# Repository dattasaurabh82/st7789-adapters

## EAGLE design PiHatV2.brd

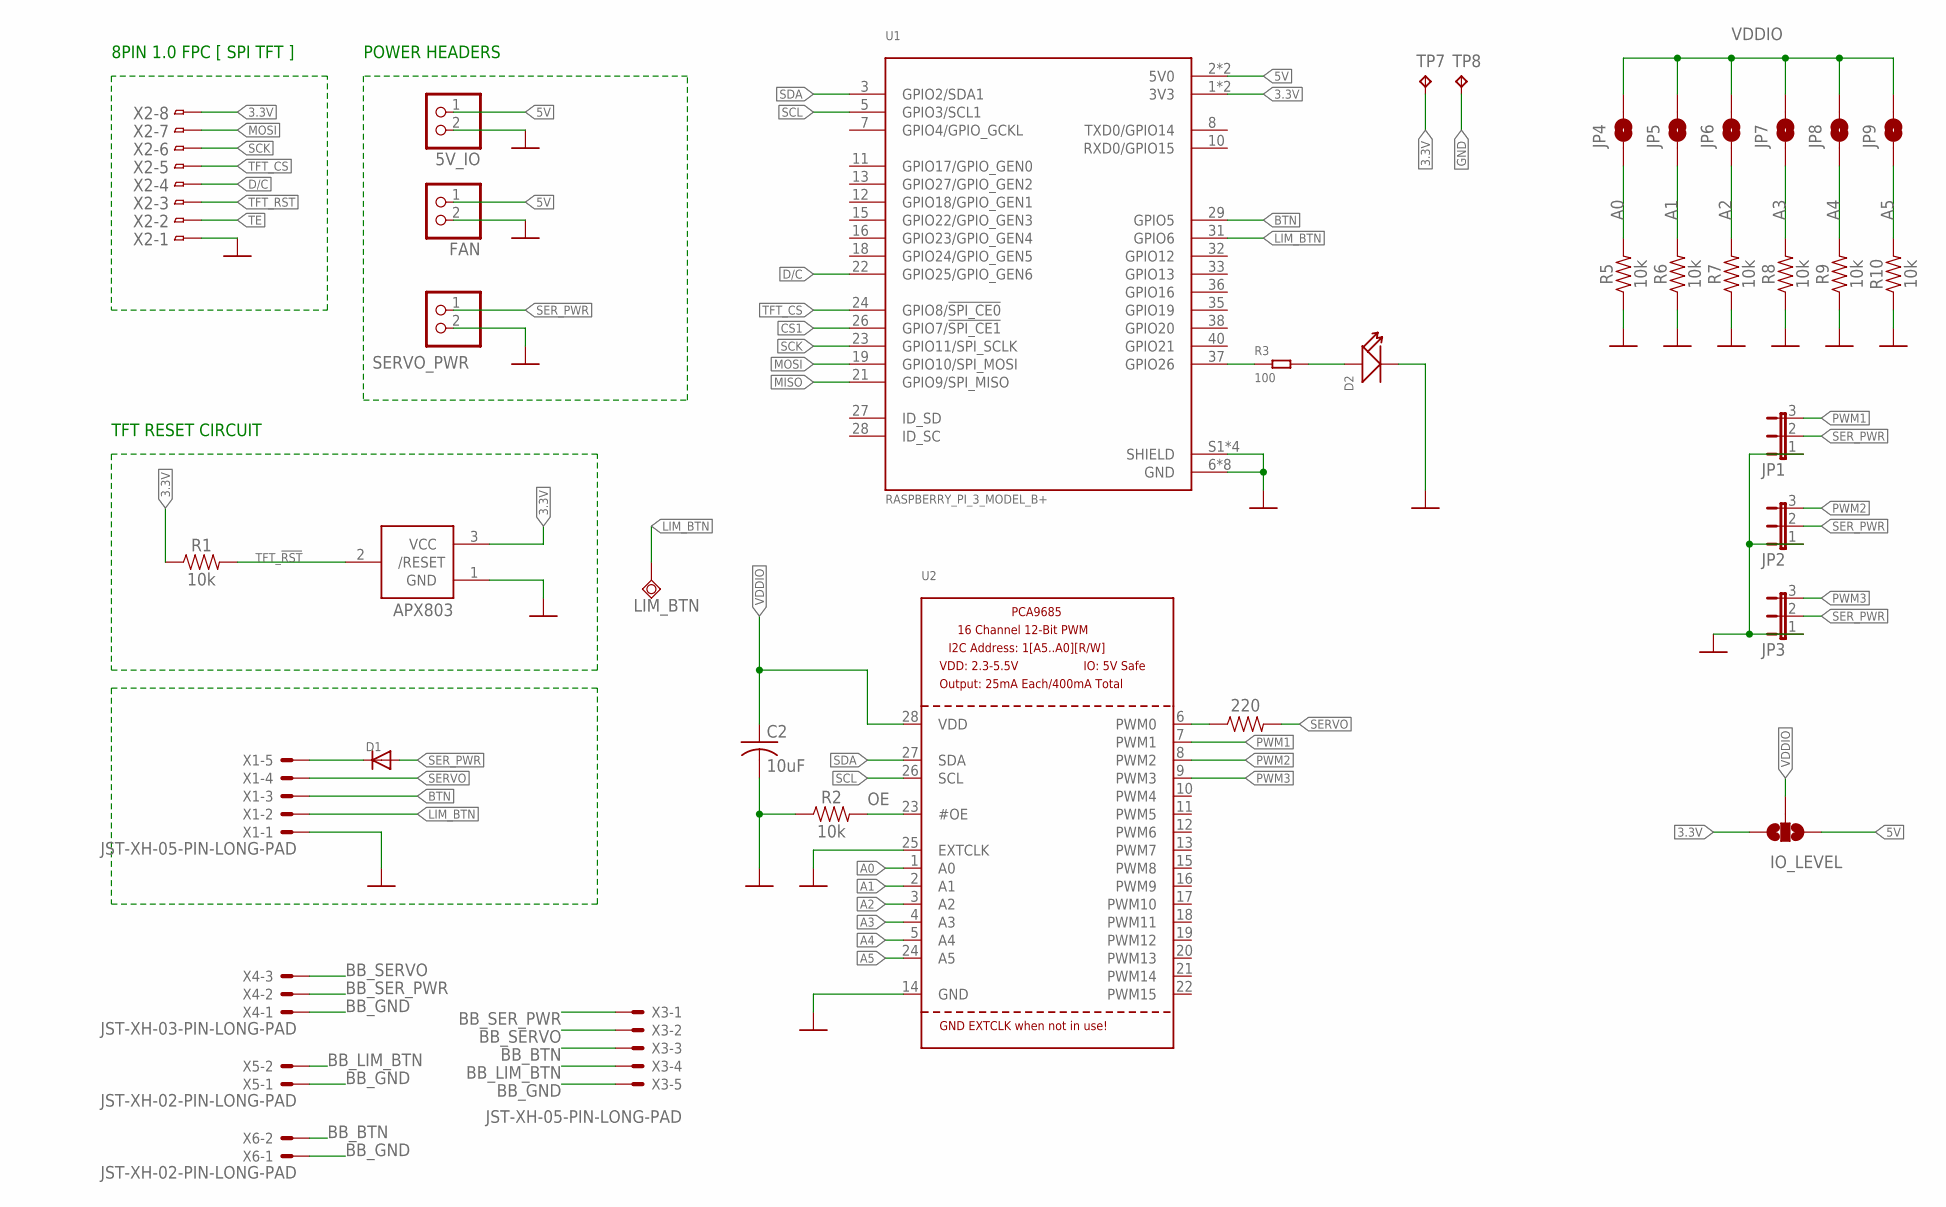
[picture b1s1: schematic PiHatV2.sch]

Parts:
5V_IO: ONBOARDCONTROLINTERFACE_LED-BADGE_SCHEMATIC_ADAFR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; ONBOARDCONTROLINTERFACE_LED-BADGE_SCHEMATIC_ADAFRUIT_JST-PH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
APX803: ADAFRUIT_AXP083-SAG; ADAFRUIT_SOT23
C2: 10uF; C0805K
D1: DIODESMA; SMADIODE
D2: BLUE-0603; LED-0603
FAN: ONBOARDCONTROLINTERFACE_LED-BADGE_SCHEMATIC_ADAFR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; ONBOARDCONTROLINTERFACE_LED-BADGE_SCHEMATIC_ADAFRUIT_JST-PH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
IO_LEVEL: JUMPER-SMT_3_NO_NO-SILK; SMT-JUMPER_3_NO_NO-SILK
JP1, JP2, JP3: LED-BADGE_SCHEMATIC_JUMPER_JP2E; LED-BADGE_SCHEMATIC_JUMPER_JP2
JP4, JP5, JP6, JP7, JP8, JP9: JUMPER-SMT_2_NO_NO-SILK; SMT-JUMPER_2_NO_NO-SILK
LIM_BTN: TESTPAD_TPSQB1,27; TESTPAD_B1,27
R1, R2, R5, R6, R7, R8, R9, R10: 10k; ARDUINO_3V_TTL_INTERFACE_2_PI_SPARKFUN-RESISTORS_0603:1
R3: 100; R0805
R4: 220; ARDUINO_3V_TTL_INTERFACE_2_PI_SPARKFUN-RESISTORS_0603:1
SERVO_PWR: ONBOARDCONTROLINTERFACE_LED-BADGE_SCHEMATIC_ADAFR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; ONBOARDCONTROLINTERFACE_LED-BADGE_SCHEMATIC_ADAFRUIT_JST-PH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
TP7, TP8: TPB2,54; B2,54
U1: RASPBERRY_PI_3_MODEL_B+; MODULE_RASPBERRY_PI_3_MODEL_B+
U2: PCA9685; TSSOP28
X1, X3: JST-XH-05-PIN-LONG-PAD; JST-XH-05-PACKAGE-LONG-PAD
X2: SCREENBREAKOUT_SCREENBREAKOUT_LEDMATRIXFPCCONNECT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; SCREENBREAKOUT_SCREENBREAKOUT_LEDMATRIXFPCCONNECTOR_CON-HIR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
X4: JST-XH-03-PIN-LONG-PAD; JST-XH-03-PACKAGE-LONG-PAD
X5, X6: JST-XH-02-PIN-LONG-PAD; JST-XH-02-PACKAGE-LONG-PAD

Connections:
3.3V: APX803.3 (VCC), IO_LEVEL.3, R1.1, TP7.TP, U1.1 (3V3), U1.17 (3V3), X2.8
5V: 5V_IO.1 (2), FAN.1 (2), IO_LEVEL.1, U1.2 (5V0), U1.4 (5V0)
A0: JP4.1, R5.2, U2.1 (A0)
A1: JP5.1, R6.2, U2.2 (A1)
A2: JP6.1, R7.2, U2.3 (A2)
A3: JP7.1, R8.2, U2.4 (A3)
A4: JP8.1, R9.2, U2.5 (A4)
A5: JP9.1, R10.2, U2.24 (A5)
BB_BTN: X3.3, X6.2
BB_GND: X3.5, X4.1, X5.1, X6.1
BB_LIM_BTN: X3.4, X5.2
BB_SERVO: X3.2, X4.3
BB_SER_PWR: X3.1, X4.2
BTN: U1.29 (GPIO5), X1.3
CS1: U1.26 (GPIO7/!SPI_CE1!)
D/C: U1.22 (GPIO25/GPIO_GEN6), X2.4
GND: 5V_IO.2 (1), APX803.1 (GND), C2.2, D2.-, FAN.2 (1), JP1.1, JP2.1, JP3.1, R2.1, R5.1, R6.1, R7.1, R8.1, R9.1, R10.1, SERVO_PWR.2 (1), TP8.TP, U1.6 (GND), U1.9 (GND), U1.14 (GND), U1.20 (GND), U1.25 (GND), U1.30 (GND), U1.34 (GND), U1.39 (GND), U1.S1 (SHIELD), U1.S2 (SHIELD), U1.S3 (SHIELD), U1.S4 (SHIELD), U2.14 (GND), U2.25 (EXTCLK), X1.1, X2.1
LIM_BTN: LIM_BTN.TP, U1.31 (GPIO6), X1.2
MISO: U1.21 (GPIO9/SPI_MISO)
MOSI: U1.19 (GPIO10/SPI_MOSI), X2.7
unnamed: R4.1, U2.6 (PWM0)
unnamed: D1.C, X1.5
unnamed: R3.1, U1.37 (GPIO26)
unnamed: D2.+, R3.2
OE: R2.2, U2.23 (#OE)
PWM1: JP1.3, U2.7 (PWM1)
PWM2: JP2.3, U2.8 (PWM2)
PWM3: JP3.3, U2.9 (PWM3)
SCK: U1.23 (GPIO11/SPI_SCLK), X2.6
SCL: U1.5 (GPIO3/SCL1), U2.26 (SCL)
SDA: U1.3 (GPIO2/SDA1), U2.27 (SDA)
SERVO: R4.2, X1.4
SER_PWR: D1.A, JP1.2, JP2.2, JP3.2, SERVO_PWR.1 (2)
TE: X2.2
TFT_!RST: APX803.2 (/RESET), R1.2, X2.3
TFT_CS: U1.24 (GPIO8/!SPI_CE0!), X2.5
VDDIO: C2.1, IO_LEVEL.2, JP4.2, JP5.2, JP6.2, JP7.2, JP8.2, JP9.2, U2.28 (VDD)

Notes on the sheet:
TFT RESET CIRCUIT
8PIN 1.0 FPC [ SPI TFT ]
POWER HEADERS

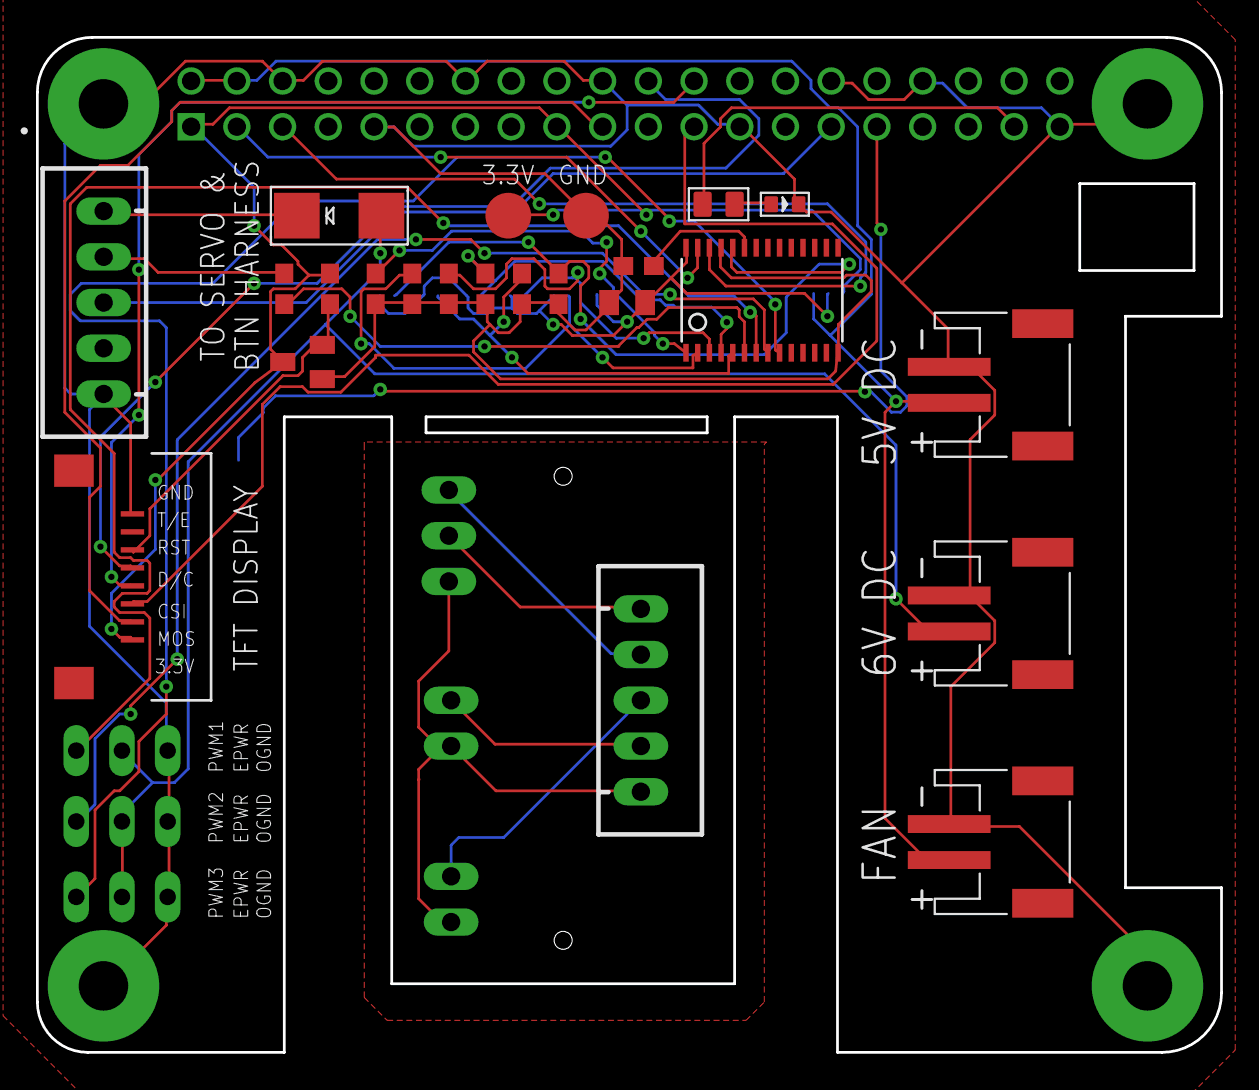
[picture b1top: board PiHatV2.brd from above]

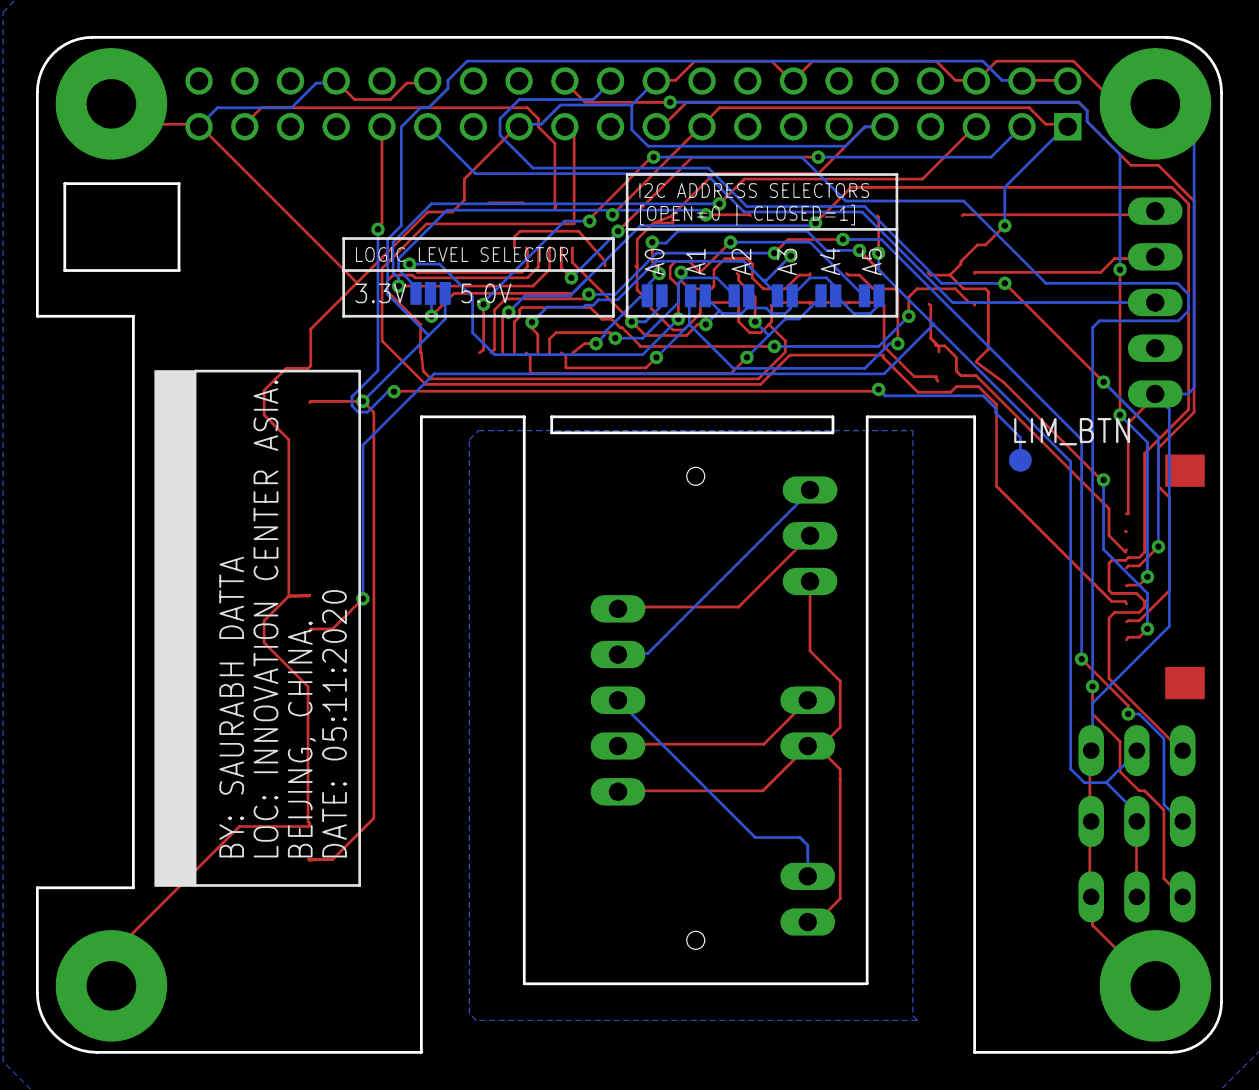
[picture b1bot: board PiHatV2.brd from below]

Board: 2 copper layers, 65.8 x 56.4 mm, 38 parts (8 on the bottom side), 34 nets.

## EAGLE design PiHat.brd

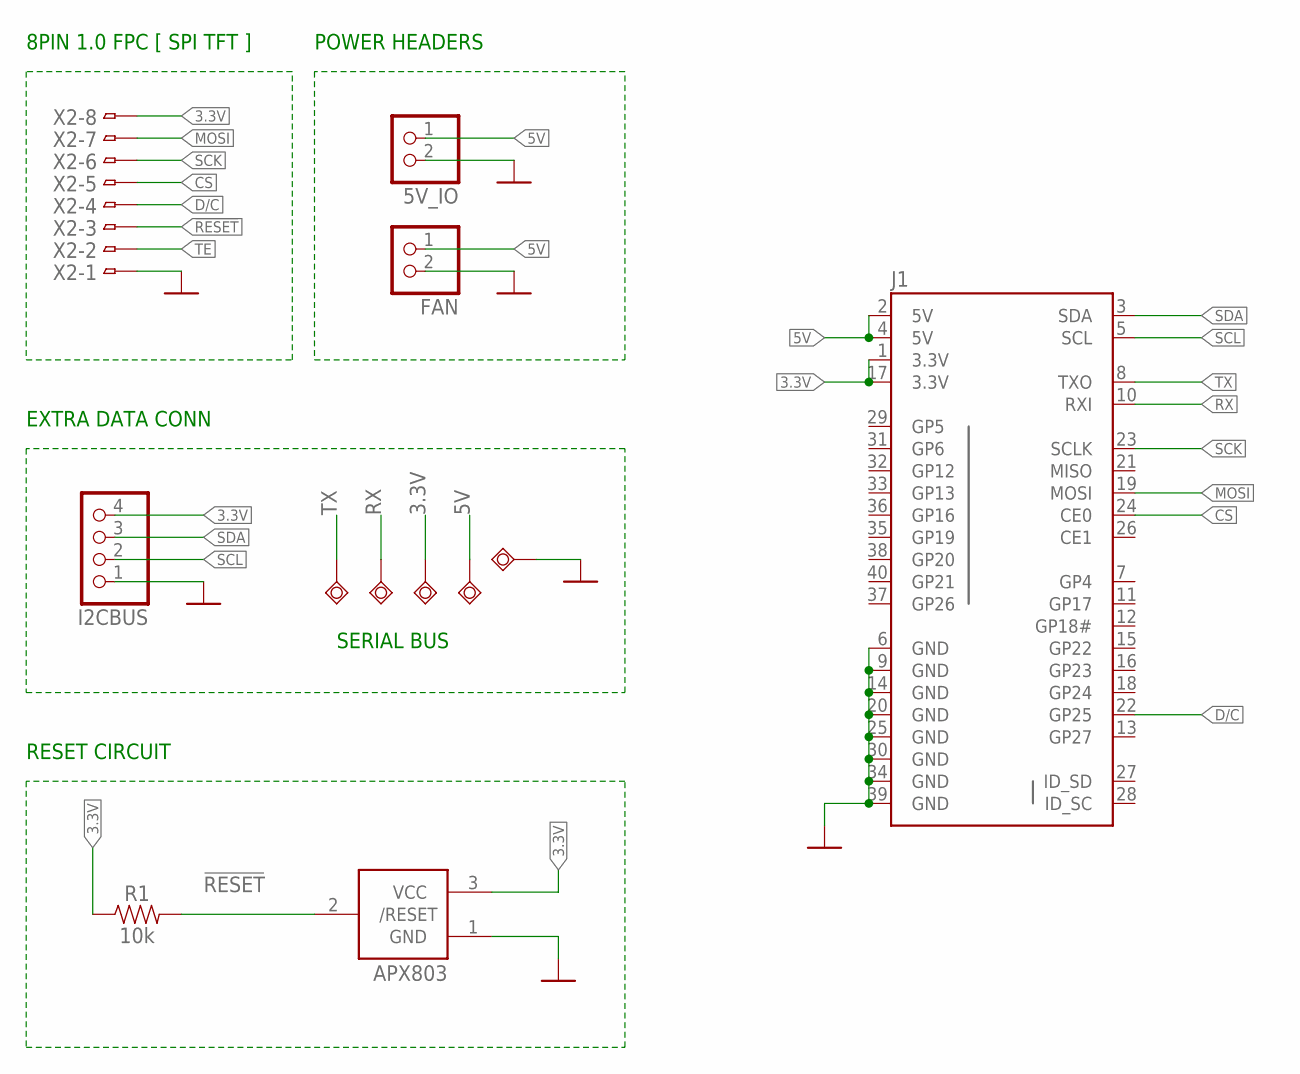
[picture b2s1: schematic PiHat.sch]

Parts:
5V_IO: ONBOARDCONTROLINTERFACE_LED-BADGE_SCHEMATIC_ADAFR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; ONBOARDCONTROLINTERFACE_LED-BADGE_SCHEMATIC_ADAFRUIT_JST-PH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
APX803: ADAFRUIT_AXP083-SAG; ADAFRUIT_SOT23
FAN: ONBOARDCONTROLINTERFACE_LED-BADGE_SCHEMATIC_ADAFR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; ONBOARDCONTROLINTERFACE_LED-BADGE_SCHEMATIC_ADAFRUIT_JST-PH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
I2CBUS: MICROBUILDER_JST_4PIN; MICROBUILDER_JSTPH4
J1: DESTINYSENSORFINAL_SPARKFUN-CONNECTORS_RASPBERRYP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; DESTINYSENSORFINAL_SPARKFUN-CONNECTORS_2X20
R1: 10k; ARDUINO_3V_TTL_INTERFACE_2_PI_SPARKFUN-RESISTORS_0603:1
TP1, TP2, TP3, TP4, TP5: DESTINYSENSORFINAL_ARDUINO_3V_TTL_INTERFACE_2_PI_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; DESTINYSENSORFINAL_ARDUINO_3V_TTL_INTERFACE_2_PI_TESTPAD_TP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
X2: SCREENBREAKOUT_SCREENBREAKOUT_LEDMATRIXFPCCONNECT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; SCREENBREAKOUT_SCREENBREAKOUT_LEDMATRIXFPCCONNECTOR_CON-HIR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

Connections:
3.3V: APX803.3 (VCC), I2CBUS.4, J1.1 (3.3V), J1.17 (3.3V), R1.1, TP3.TP, X2.8
5V: 5V_IO.1 (2), FAN.1 (2), J1.2 (5V), J1.4 (5V), TP4.TP
!RESET: APX803.2 (/RESET), R1.2, X2.3
CS: J1.24 (CE0), X2.5
D/C: J1.22 (GP25), X2.4
GND: 5V_IO.2 (1), APX803.1 (GND), FAN.2 (1), I2CBUS.1, J1.6 (GND), J1.9 (GND), J1.14 (GND), J1.20 (GND), J1.25 (GND), J1.30 (GND), J1.34 (GND), J1.39 (GND), TP5.TP, X2.1
MOSI: J1.19 (MOSI), X2.7
RX: J1.10 (RXI), TP2.TP
SCK: J1.23 (SCLK), X2.6
SCL: I2CBUS.2, J1.5 (SCL)
SDA: I2CBUS.3, J1.3 (SDA)
TE: X2.2
TX: J1.8 (TXO), TP1.TP

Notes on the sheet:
SERIAL BUS
RESET CIRCUIT
8PIN 1.0 FPC [ SPI TFT ]
POWER HEADERS
EXTRA DATA CONN

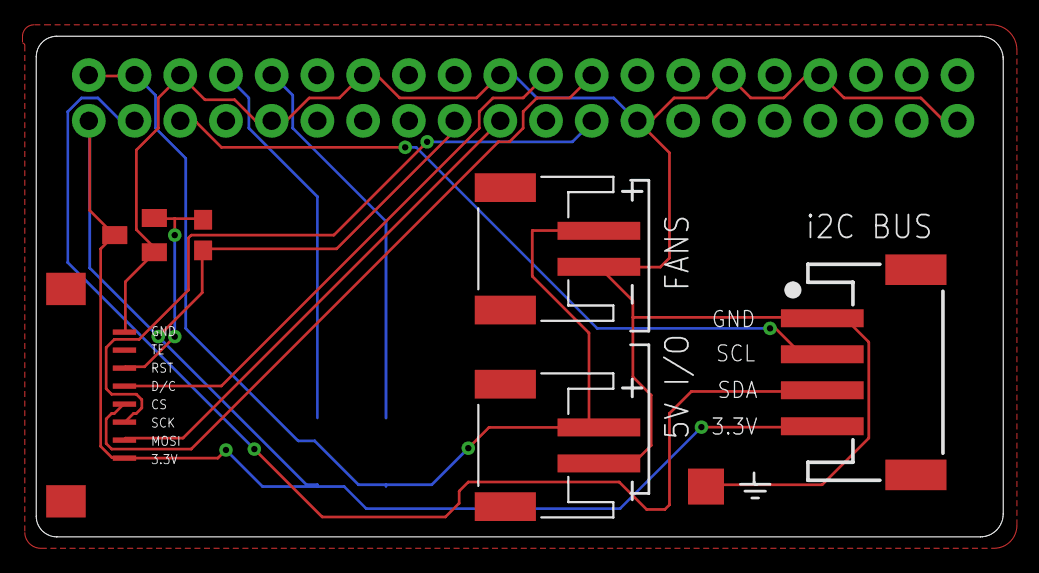
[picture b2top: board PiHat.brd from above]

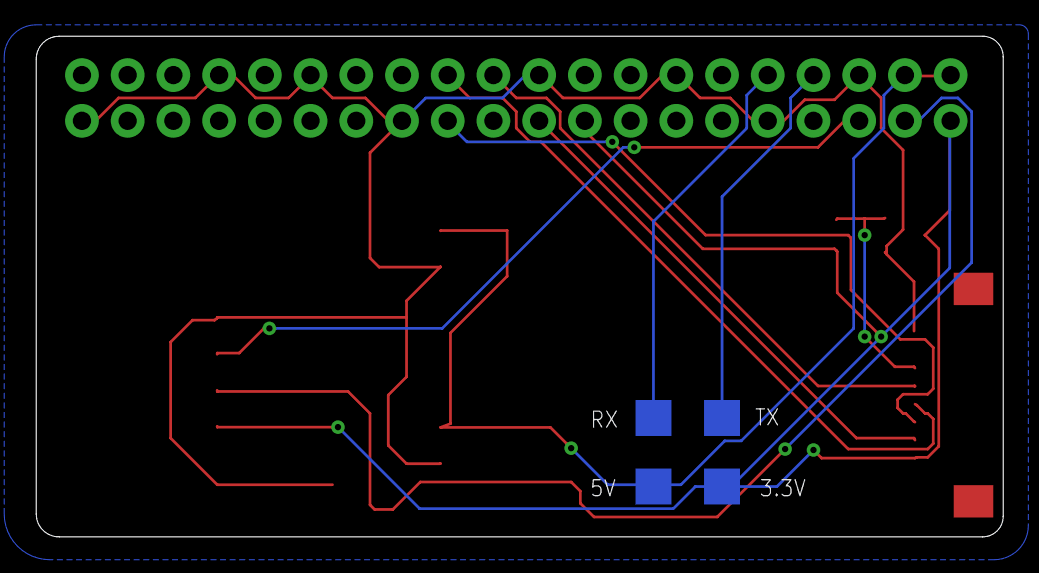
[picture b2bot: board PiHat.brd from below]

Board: 2 copper layers, 53.7 x 27.8 mm, 12 parts (4 on the bottom side), 12 nets.

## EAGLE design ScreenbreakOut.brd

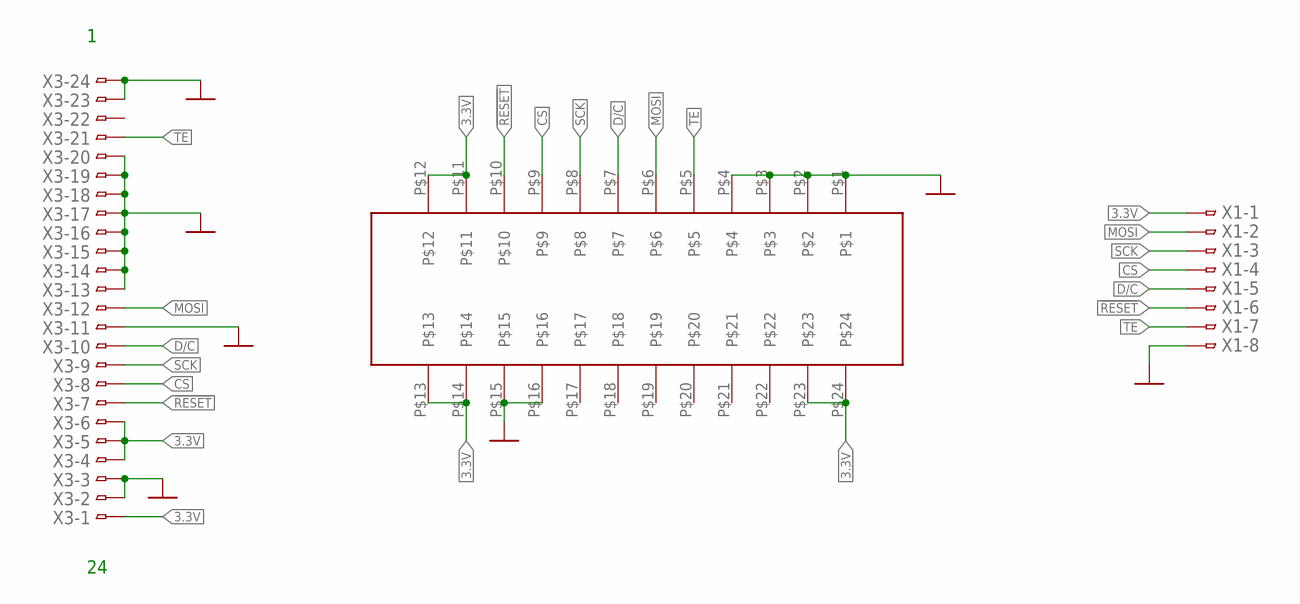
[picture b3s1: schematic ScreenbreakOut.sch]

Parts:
U$1: CICULARSCREENRELATED_OK-14F24-04
X1: SCREENBREAKOUT_LEDMATRIXFPCCONNECTOR_CON-HIROSE_F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; SCREENBREAKOUT_LEDMATRIXFPCCONNECTOR_CON-HIROSE_FH12-08S-1SH
X3: CON-HIROSE_FH12-24S-0.5SH

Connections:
3.3V: U$1.P$11, U$1.P$12, U$1.P$13, U$1.P$14, U$1.P$23, U$1.P$24, X1.1, X3.1, X3.4, X3.5, X3.6
!RESET: U$1.P$10, X1.6, X3.7
CS: U$1.P$9, X1.4, X3.8
D/C: U$1.P$7, X1.5, X3.10
GND: U$1.P$1, U$1.P$2, U$1.P$3, U$1.P$4, U$1.P$15, U$1.P$16, X1.8, X3.2, X3.3, X3.11, X3.13, X3.14, X3.15, X3.16, X3.17, X3.18, X3.19, X3.20, X3.23, X3.24
MOSI: U$1.P$6, X1.2, X3.12
SCK: U$1.P$8, X1.3, X3.9
TE: U$1.P$5, X1.7, X3.21

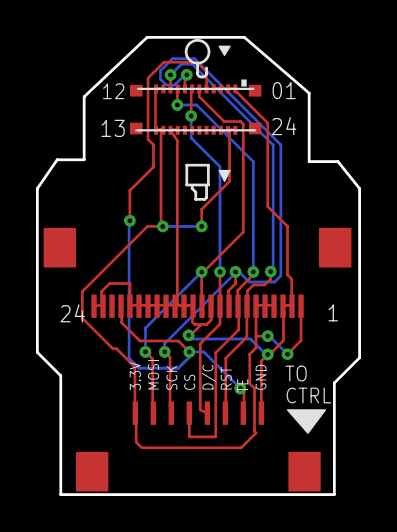
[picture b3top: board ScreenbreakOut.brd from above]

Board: 2 copper layers, 17.9 x 25.4 mm, 3 parts (0 on the bottom side), 8 nets.

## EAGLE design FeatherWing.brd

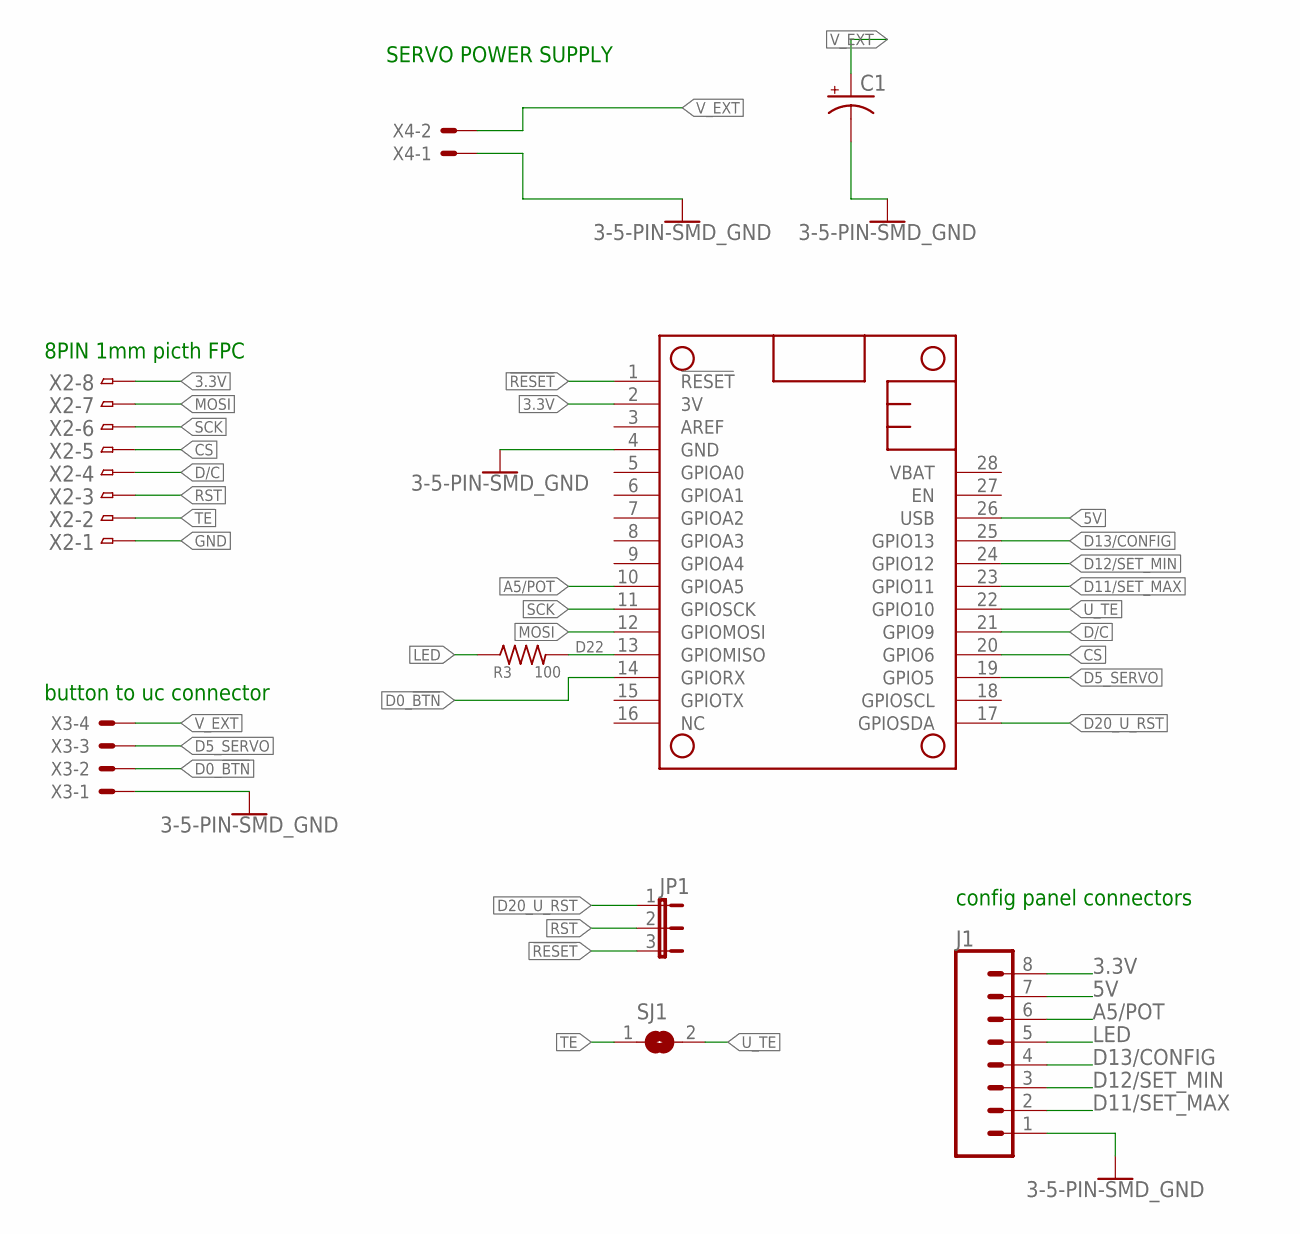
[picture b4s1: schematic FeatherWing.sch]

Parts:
C1: ADAFRUIT_CNCT_NFP_CPOL-USC/6032-28R; ADAFRUIT_CNCT_NFP_C/6032-28R
J1: SPARKFUN-CONNECTORS_CONN_08LONGPADS; SPARKFUN-CONNECTORS_1X08_LONGPADS
JP1: LED-BADGE_SCHEMATIC_JUMPER_JP2E; LED-BADGE_SCHEMATIC_JUMPER_JP2
MS1: ADAFRUIT_FEATHERWING
R3: 100; AIRPOCKETCELL_ARDUINO_3V_TTL_INTERFACE_2_PI_ADAFRUIT_M0805
SJ1: AIRPOCKETCELL_JUMPER_SJW
X2: LEDMATRIXFPCCONNECTOR_CON-HIROSE_FH12-08S-1SH
X3: REMBRANDT-ELECTRONICS---JST-XH-CONNECTORS-V1-0_JS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; REMBRANDT-ELECTRONICS---JST-XH-CONNECTORS-V1-0_JST-XH-04-PA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
X4: REMBRANDT-ELECTRONICS---JST-XH-CONNECTORS-V1-0_JS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; REMBRANDT-ELECTRONICS---JST-XH-CONNECTORS-V1-0_JST-XH-02-PA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

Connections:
3.3V: J1.8, MS1.2 (3V), X2.8
5V: J1.7, MS1.26 (USB)
!RESET: JP1.3, MS1.1 (!RESET)
A5/POT: J1.6, MS1.10 (GPIOA5)
CS: MS1.20 (GPIO6), X2.5
D0_!BTN: MS1.14 (GPIORX), X3.2
D5_SERVO: MS1.19 (GPIO5), X3.3
D11/SET_MAX: J1.2, MS1.23 (GPIO11)
D12/SET_MIN: J1.3, MS1.24 (GPIO12)
D13/CONFIG: J1.4, MS1.25 (GPIO13)
D20_U_RST: JP1.1, MS1.17 (GPIOSDA)
D22: MS1.13 (GPIOMISO), R3.2
D/C: MS1.21 (GPIO9), X2.4
GND: C1.-, J1.1, MS1.4 (GND), X2.1, X3.1, X4.1
LED: J1.5, R3.1
MOSI: MS1.12 (GPIOMOSI), X2.7
RST: JP1.2, X2.3
SCK: MS1.11 (GPIOSCK), X2.6
TE: SJ1.1, X2.2
U_TE: MS1.22 (GPIO10), SJ1.2
V_EXT: C1.+, X3.4, X4.2

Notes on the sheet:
8PIN 1mm picth FPC
config panel connectors
SERVO POWER SUPPLY
button to uc connector

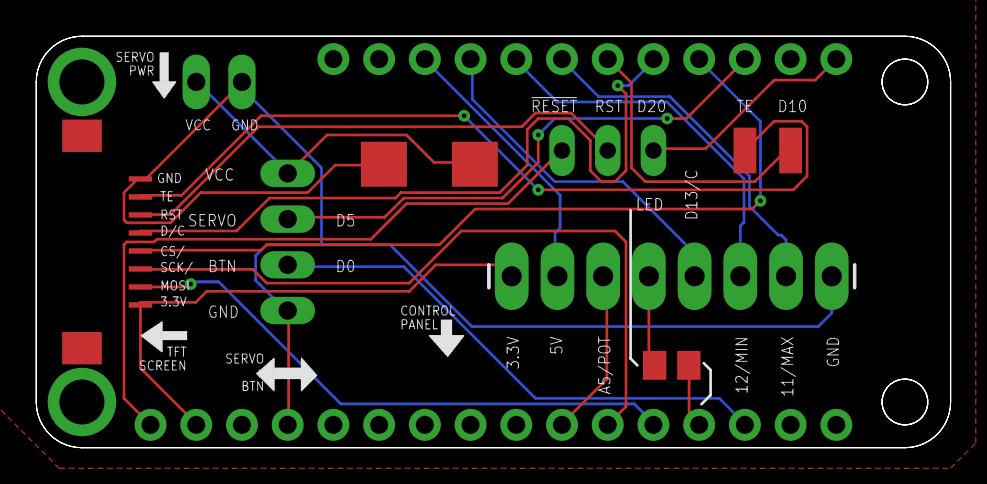
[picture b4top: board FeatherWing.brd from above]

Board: 2 copper layers, 50.8 x 22.9 mm, 9 parts (0 on the bottom side), 21 nets.

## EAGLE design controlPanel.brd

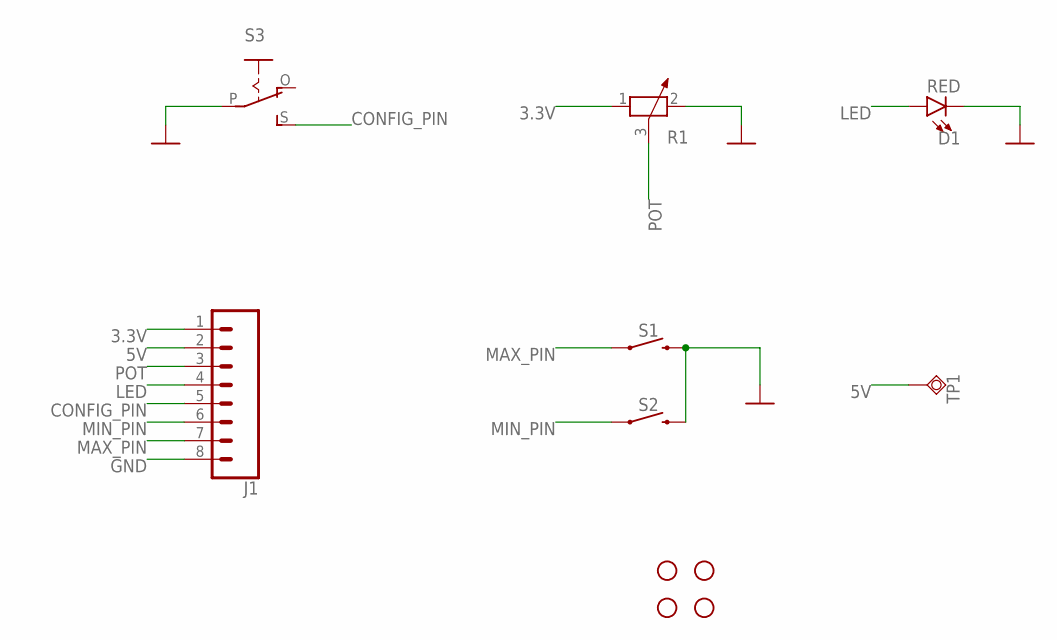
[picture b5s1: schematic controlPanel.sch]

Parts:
D1: RED; SPARKFUN-LED_LED-0603
H1, H2, H3, H4: STAND-OFFTIGHT; STAND-OFF-TIGHT
J1: CONN_08SMD-COMBO-FEMALE; 1X08_SMD_COMBINED
R1: RCL_POTENTIOMETER_PT-10; RCL_PT-10
S1, S2: SPARKFUN-SWITCHES_MOMENTARY-SWITCH-SPST-PTH-12MM; SPARKFUN-SWITCHES_TACTILE_SWITCH_PTH_12MM
S3: ADAFRUIT_EG1218S; ADAFRUIT_EG1218
TP1: TESTPAD_TPSQTP20R; TESTPAD_TP20R

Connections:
3.3V: J1.1, R1.1
5V: J1.2, TP1.TP
CONFIG_PIN: J1.5, S3.S
GND: D1.C, J1.8, R1.2, S1.3 (2), S2.3 (2), S3.P
LED: D1.A, J1.4
MAX_PIN: J1.7, S1.1
MIN_PIN: J1.6, S2.1
POT: J1.3, R1.3

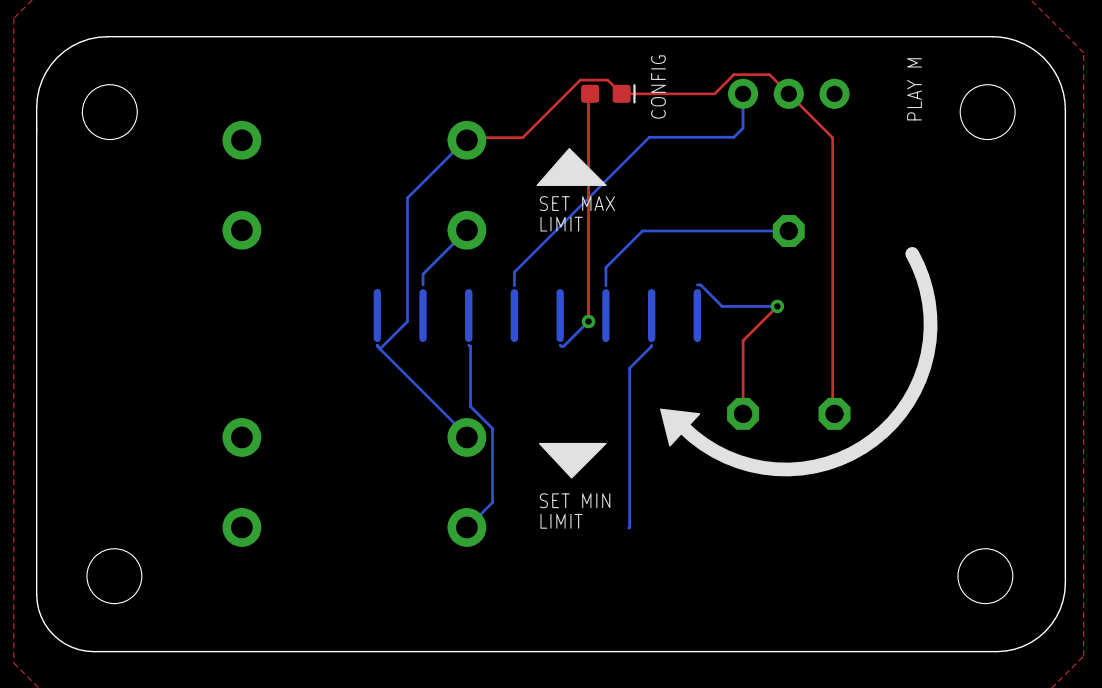
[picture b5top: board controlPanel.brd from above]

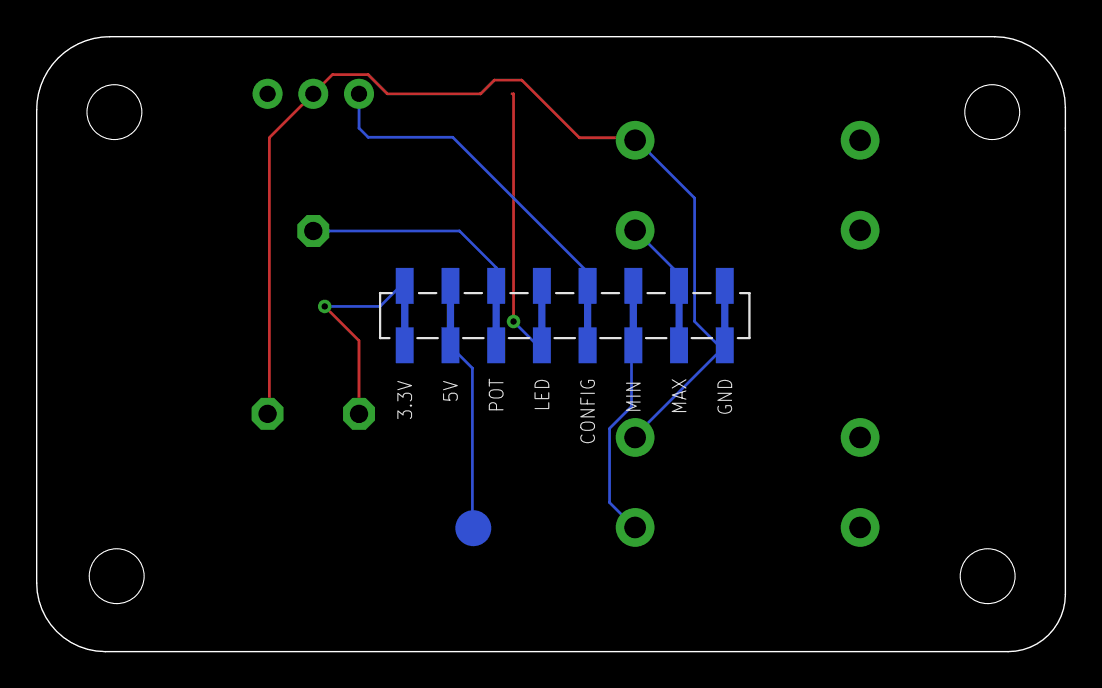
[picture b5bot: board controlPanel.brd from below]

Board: 2 copper layers, 57.1 x 34.2 mm, 11 parts (2 on the bottom side), 8 nets.

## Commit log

2020-10-28 first commit ever
2020-11-05 pi HAT with preipherals for the office project need
2020-12-15 support for a limit switch button for cont servo

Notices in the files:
parts and their libraries:
SparkFun-Aesthetics: Licensing: Creative Commons ShareAlike 4.0 International - https://creativecommons.org/licenses/by-sa/4.0
